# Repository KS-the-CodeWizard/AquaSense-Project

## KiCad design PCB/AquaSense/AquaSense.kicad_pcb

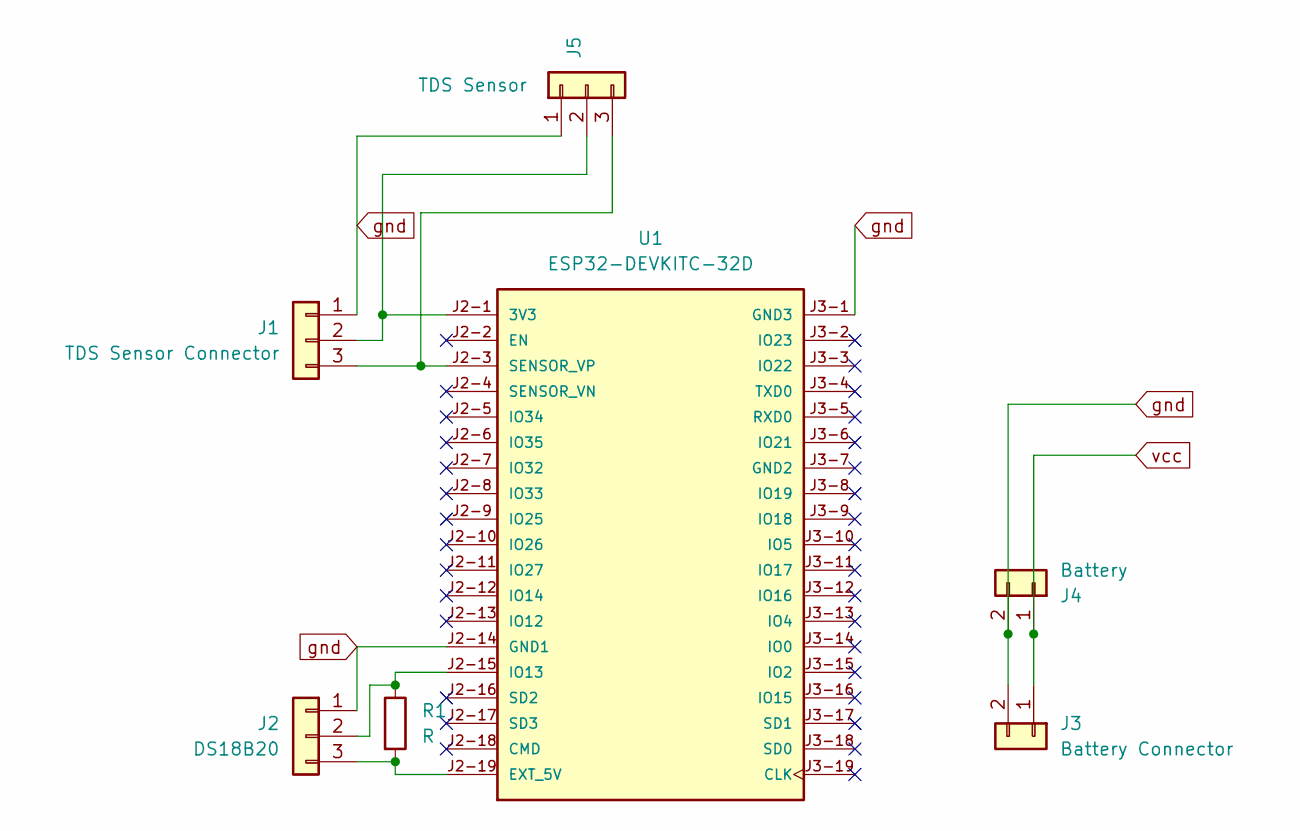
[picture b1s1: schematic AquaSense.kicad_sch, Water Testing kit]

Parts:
J1: TDS Sensor Connector; PinHeader_1x03_P2.54mm_Vertical
J2: DS18B20; PinHeader_1x03_P2.54mm_Vertical
J3: Battery Connector; PinHeader_1x02_P2.54mm_Vertical
J4: Battery; PinHeader_1x02_P2.54mm_Vertical
J5: TDS Sensor; PinHeader_1x03_P2.54mm_Vertical
R1: R; R_Axial_DIN0411_L9.9mm_D3.6mm_P15.24mm_Horizontal
U1: ESP32-DEVKITC-32D; MODULE_ESP32-wroom32; PARTREV V4

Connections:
unnamed: J1.2, J5.2, U1.J2-1 (3V3)
unnamed: J1.3, J5.3, U1.J2-3 (SENSOR_VP)
unnamed: J2.2, R1.1, U1.J2-15 (IO13)
unnamed: J2.3, R1.2, U1.J2-19 (EXT_5V)
gnd: J1.1, J2.1, J3.2, J4.2, J5.1, U1.J2-14 (GND1), U1.J3-1 (GND3)
vcc: J3.1, J4.1

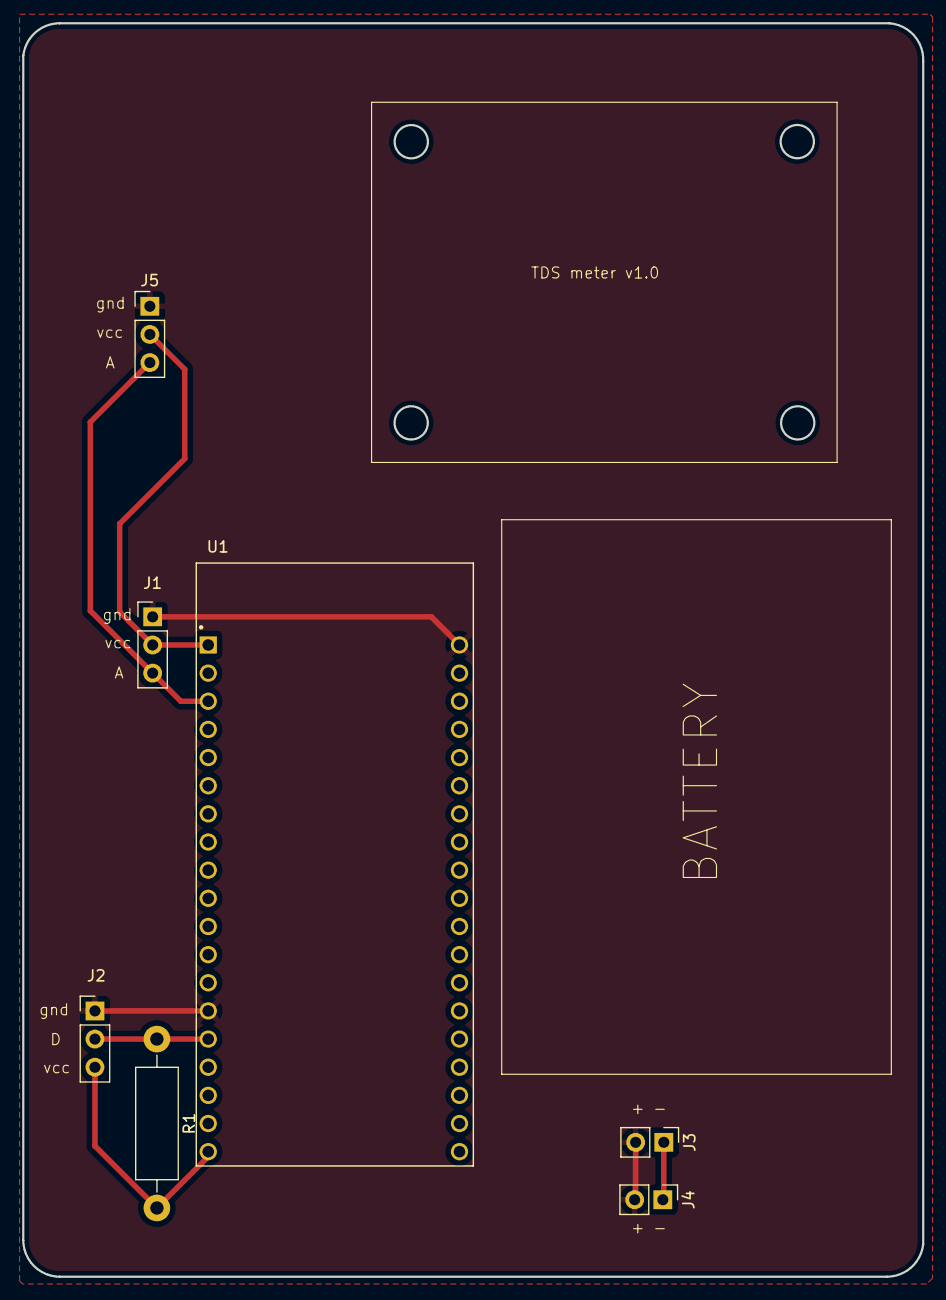
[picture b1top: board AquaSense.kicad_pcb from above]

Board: 2 copper layers, 81.2 x 113.1 mm, 7 parts (0 on the bottom side), 6 nets.
